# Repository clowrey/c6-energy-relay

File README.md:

# C6 Energy Relay

A Wi-Fi energy meter with two relays, for Home Assistant through ESPHome. It measures the line
voltage and two CT-clamp currents, reports power and energy for each, and switches two loads (or two
contactor coils). It is designed for JLCPCB to build fully assembled. It sits on a DIN rail in a
3D-printed case, inside a plastic junction box.

> **Status:** the design is finished and checked by its own tests (KiCad ERC and DRC with creepage
> rules, schematic parity, JLC files, case fit, ESPHome config). No boards have been made or tested
> yet. Treat it as an untested design: check it yourself before you build one and connect it to
> mains.

| | |
|---|---|
| MCU | ESP32-C5 (DOIT ESPC5-32-H4, 4 MB flash): dual-band 2.4 + 5 GHz Wi-Fi 6, BLE, 802.15.4 (Thread/Zigbee capable), PCB antenna |
| Metering | BL0939 on UART: voltage, 2 × current, 2 × active power, 2 × energy |
| Voltage sense | ZMPT107-1 current-type transformer, fed through 4 × 100 kΩ from the line |
| Current sense | 2 CT clamps with bare leads (100 A : 50 mA type, e.g. SCT-013-000), 0.6 Ω burden each |
| Relays | 2 × Hongfa HF32FV-16 (16 A SPST-NO), dry contacts, for loads up to 10 A |
| Supply | 100–240 V AC: 120 V line–neutral or 240 V leg–leg, chosen at install. HLK-PM01 isolated 5 V, or USB-C on the bench |
| Terminals | all pluggable: 3 × 5.08 mm 15 A (mains in, relay 1, relay 2), 1 × 3.81 mm 4-pole (CTs) |
| GPIO | every unused GPIO on a 2 × 8 header footprint (holes only, nothing fitted) |
| Qwiic | one Qwiic / STEMMA QT port (JST SH, 3.3 V I2C on GPIO2 / GPIO3, 4.7 kΩ pull-ups) |
| Board | 76.4 × 80 mm, 2 layers, every part on the top side, cut away under the antenna |
| Cost | about $14.70 a board for 30, $11.90 for 100, assembled with plugs (estimate, see [below](#ordering-at-jlcpcb)) |

**Contents:** [How it works](#how-it-works) · [Schematic](#schematic) · [Circuit board](#circuit-board) ·
[Case](#case) · [Safety](#safety) · [Wiring](#wiring) · [Firmware](#firmware) ·
[Ordering](#ordering-at-jlcpcb) · [Building from source](#building-it-from-source) · [Licence](#licence)

## How it works

Everything that touches mains is on the left, and everything you can touch (USB-C, the CT terminal,
the GPIO header) is on the right. Three parts bridge the two sides, and each is rated for it: the
HLK-PM01 power module, the ZMPT107-1 voltage transformer and the relays (coil to contact). On the
board the two sides are kept 6.5 mm apart.

- **Power:** the mains input goes through a 1 A slow SMD fuse in **each** line, so a 240 V leg–leg install
  is fused on both legs. The fuses are Hongda 40T ceramic types rated to break 1000 A at 250 V AC (the
  varistor can fail as a short across the line); Littelfuse's 443 fits the same pads but breaks only
  50 A. No copper runs under them. A 10D561K varistor (MOV) clamps surges after the fuses. The potted
  HLK-PM01 makes an isolated 5 V, 600 mA, with a 220 µF solid polymer capacitor on it. On the bench, USB-C powers the board through an SS14 diode
  instead. An AMS1117-3.3 LDO (a JLC Basic part) makes 3.3 V for the ESP32 and the BL0939. Its dropout
  is 1.1 V at 800 mA, and from USB the diode leaves about 4.5 V, so it still regulates through the
  module's 5 GHz transmit peaks (about 400 mA), with little to spare. Its tab sits on a 3.3 V copper area
  that spreads its heat.
- **Voltage:** four 100 kΩ 1206 resistors in series feed about 0.6 mA at 240 V (0.3 mA at 120 V) from the line into
  the ZMPT107-1, a 2 mA : 2 mA current transformer. Its secondary drives a 51 Ω load, and the BL0939 reads
  that voltage on VP (31 mV at 240 V, 34 mV at 264 V). At 120 V the signal is half the 240 V one;
  calibration covers both. The four resistors turn 0.14 W into heat at 240 V (0.04 W at 120 V).
- **Current:** each CT clamp (50 mA at 100 A) works into a 0.6 Ω burden (two 0.3 Ω 1 % resistors,
  centre to ground) right at the terminal, then ferrite beads and a 1 kΩ / 47 nF filter into the
  BL0939. The beads carry only the BL0939's input current, so a failed bead can't open the CT.
- **Metering:** the BL0939 measures continuously and sends readings over a UART (GPIO1 TX, GPIO0 RX, 4800 baud)
  to the ESP32-C5, which runs ESPHome and reports to Home Assistant.
- **Relays:** each relay coil runs from 5 V through an MMBT3904 transistor (470 Ω base resistor,
  about 5 mA, so it saturates fully at the coil's 80–93 mA; 10 kΩ pull-down so it stays off while
  the ESP32 boots) with a 1N4148W flyback diode. GPIO6 and
  GPIO12 drive them. The firmware gives a coil full voltage for 0.3 s, then holds it with PWM at 60 %
  (the relay's datasheet allows a hold at half the rated voltage), so a held coil makes about a third of
  the heat: roughly 0.15 W instead of 0.4 W. The contacts are dry: COM and NO go to their own terminal and switch whatever
  you wire through them.
- **USB-C** goes straight to the ESP32-C5's native USB (GPIO13/14, through 22 Ω series resistors; there is no ESD protection chip),
  for flashing and logs without a USB-serial chip or buttons.

## Schematic

The full schematic is in [`hw/out/schematic.pdf`](hw/out/schematic.pdf) (KiCad 10:
[`hw/c6-energy-relay.kicad_sch`](hw/c6-energy-relay.kicad_sch)). It is generated from
[`hw/design.py`](hw/design.py), one functional block per section, and every pin connects by a net
label.

<details>
<summary><b>Each section, larger</b></summary>

**Mains input, fuses, MOV and the isolated 5 V supply**

**Voltage sense:** the divider into the ZMPT107-1, and its 51 Ω load

**BL0939 metering and the CT inputs**

**5 V and 3.3 V**

**USB-C** (native USB, series resistors, the SS14 power diode)

**ESP32-C5 module, EN and BOOT buttons, status LED, the Qwiic port and the GPIO header**

**Relays and their drivers**

</details>

## Circuit board

76.4 × 80 mm, 2 layers, 1.6 mm, every part on the top side. All the terminals are on the bottom edge,
from left to right: the CTs, the mains input, relay 1 and relay 2. That keeps every wire in one place,
and the low-voltage CT terminal at the far end from the relay contacts. USB-C and the Qwiic port are on
the top edge.
The plug headers stick out 3 mm past the bottom edge, flush with the outside of the case wall, and USB-C
1.25 mm past the top edge, so plugs go in easily with the case on.

The layout is three bands. Along the top: the Qwiic port, USB-C (2.5 mm apart, so both plugs fit side by
side), the LDO and the ESP32-C5 module in the top-right corner. The board is cut away under the module's
antenna (a 26.5 × 6.3 mm notch in the corner), and the copper keep-out around it reaches 3.8 mm past the
module's left side, so there is no board, copper or ground under or beside the antenna. The relays and the
power module are as far from it as the board allows. In the middle: the BL0939 and its input filters in
the left column, the HLK-PM01 beside them, and the GPIO header under the module with the EN and BOOT
buttons and the status LED next to it. Along the bottom: the CT terminal and burdens, the ZMPT107-1, the
fuses with the voltage divider between them, the varistor, and the two relays over their terminals. Every
part has its reference next to it, and the buttons, the LED and every connector pin are named on the
silkscreen.

Small parts keep at least 0.3 mm between their courtyards (the IPC-7351 outline, which already adds
0.25 mm around each part), so there is at least 0.8 mm between any two parts' bodies and pads:
more than JLC's 0.3 mm assembly minimum, with room for a soldering iron.

| Top | Bottom |
|---|---|
|  |  |

| From the front left | Terminals along the bottom edge |
|---|---|
|  |  |

**Mains spacing.** The mains parts are in the bottom half, from the input up to the HLK-PM01 (the
unpoured area on the bottom view), and the low-voltage parts around them. The rules are checked by KiCad's DRC, including its
creepage check, on every build:

| Between | Clearance and creepage |
|---|---|
| any mains net and low voltage (ground, 5 V, 3.3 V, signals) | 6.5 mm |
| L and N/L2, the input and each relay, relay 1 and relay 2 | 4 mm |
| a relay's COM and NO (the open contact sees line voltage) | 4 mm creepage, 3 mm clearance |
| L and N/L2 inside the 5.08 mm terminal and the HLK-PM01's pins | 2 mm (the parts' own pitch); a 1 mm slot between the terminal pins lengthens the surface path |
| the voltage divider's nodes, to each other and to L or N/L2 | 1.5 mm clearance (two resistors apart they see about 120 V) |

The relay contacts carry up to 10 A on 5 mm wide copper areas on both layers, with the solder mask
opened so they can be tinned thicker. The case screws pass through the four mounting holes and can be
touched from the back of the case, so every hole keeps 6.5 mm from mains copper, the same as the
low-voltage side.

**Layers.** The board is routed by hand, with no sharp bend anywhere. The tracks are listed in
[`hw/routes.py`](hw/routes.py) as waypoints, and every straight run is at 0°, 45° or 90°:
[`hw/route.py`](hw/route.py) splits any other leg into a straight run and a 45° run, cuts every right-angle
corner into two 45° bends, and rounds each bend with a small arc (0.5 mm radius for signals, 1.5 × the width
for power and mains). Where tracks run together they cross open board on long 45° runs side by side: the GPIOs
leave the module's pins at 45° and fan down to the header in two 45° bundles, the UART pair runs 45° from the
bus down to the BL0939, and the bus cuts its corners long at 45°. Lanes in a bundle keep their spacing through
every bend. Corners where another branch joins stay
sharp, so the joint stays connected. Signal tracks are 0.2 mm, and ground is poured on both layers and
stitched with vias. The LDO's tab (its 3.3 V output, and how it sheds heat) sits on a solid 3.3 V copper
area of about 46 mm².

| All copper and top silkscreen | Top copper | Bottom copper |
|---|---|---|
|  |  |  |

| Top silkscreen | Top solder mask (openings) |
|---|---|
|  |  |

The GPIO header (J6) carries 3V3, 5V, GND and GPIO 4, 7, 8, 9, 10, 11, 15, 23, 24, 25, 26 and 27. Power
comes first, then ground, then the GPIOs in the order they leave the module (one row reads 3V3, GND, 7, 9,
27, 23, 11, 26; the other 5V, GND, 8, 10, 4, 15, 24, 25), so a sensor's supply, ground and signal wires sit
side by side. GPIO27 has a 10 kΩ pull-up (R19): the ESP32-C5 needs it high at reset for USB flashing.
The Qwiic port (J7, at the left end of the top edge) is a 4-pin JST SH socket for 3.3 V I2C sensors and
displays: pin 1 GND, 2 3V3, 3 SDA (GPIO2), 4 SCL (GPIO3), with 4.7 kΩ pull-ups to 3V3. GPIO2 and GPIO3 are
strapping pins (MTMS and MTDI), but the pull-ups hold them high at reset, which is what they need there.
The silkscreen marks the strapping pins on the header (7, 25, 26, 27) with `*`: keep them free of pull-downs at reset. The top side names each plug: the CT pins
behind their terminal, `RELAY 1` / `RELAY 2` beside theirs with `COM` and `NO` each over its own contact's copper, `MAINS`, `USB` and `QWIIC`. The Qwiic pins are named in pin order below the socket (`SCL SDA 3V3 GND`)
and again on the bottom side, in the order you see them from there.
The bottom side names every terminal pin.

## Case

Three printed parts, built in build123d from the board's own dimensions ([`case/case.py`](case/case.py)):

- **Cover:** the front shell, with a pillar at each of the board's four mounting holes. The plugs
  stick out through openings in the bottom wall, USB-C and the Qwiic port through the top; the wall is solid below the
  board, so nothing slips in under it to the mains solder joints. There are vents in the top wall
  beside the USB-C and in the right wall above the relays (none beside mains parts). The front face is closed; a short tube carries the status LED's light
  to a 0.6 mm thin window. The front face names every opening and its pins (MAINS L N, RELAY 1 and 2
  COM NO, CT1 and CT2 + −, USB, QWIIC), cut 0.4 mm deep. The Qwiic opening is 13 × 8 mm: the small plug ends
  inside the wall, so the opening leaves 3 mm each side to grip it, and it is too low for a finger.
- **Base:** the sealed back plate. Its only openings are the four screw holes, so nothing pushed in
  from the back (a screwdriver, the metal DIN rail) can reach the mains parts behind the board. A
  standoff rises from it to each mounting hole, and a rim locates it inside the cover's walls. A
  0.4 mm deep pocket in its back gives the clip's moving parts room to slide.
- **DIN clip:** screwed under the base, it clips the case onto a TS35 rail.
  - **Hook (top):** 65 mm long, with a 3.5 mm thick wall and a 2.2 mm thick lip that reaches 2 mm
    over the rail's flange. Five ribs behind the wall stop it bending back off the rail.
  - **Latch (bottom):** a 20 mm wide block with the same wall and lip. It rides on four 1.2 mm spring
    beams cut into the clip plate, which bend in the plate's own plane, so the block slides down
    2.4 mm to clear the flange while the beams stay under half of PETG's yield strain. The beams are
    anchored clear of the screw at the left (it sits in their band), so the latch is a little right
    of centre. The
    lip's underside is a 45° ramp: rock the case onto the rail and it snaps on. Two straps printed
    over the pull tab's channel stop the latch twisting away from the case.
  - **To take it off the rail,** pull the tab at the clip's bottom edge down: put a screwdriver in
    its slot and lever.

**Four screws hold everything:** M3 × 16 countersunk, from the back through the clip, the base, its
standoff and the board, self-tapping into 2.8 mm pilot holes in the cover's pillars (no inserts). The
board is clamped between the standoffs and the pillars, and the heads sit flush in the clip. To
assemble, lay the cover face down, drop the board in (components down) onto the pillars, put the
base and then the clip on, and fit the four screws. Nothing inside the walls stands between the
board and the open back, and a test checks that.

| Exploded | Board in the cover, from the back |
|---|---|
|  |  |

| On a DIN rail, from the back | The DIN clip: ribbed hook (top), latch on its spring beams and pull tab (bottom) |
|---|---|
|  |  |

Print in PETG (the latch has to flex): 0.2 mm layers, 3 walls. Print the cover on its front face and
the base on its back face (standoffs up), both without supports. Print the clip on its flat face (hook
and latch up), so the spring beams bend along the layers, with supports under the hook's and latch's
2 mm lips only: not under the two straps over the pull tab, which bridge. STEP files and print-oriented STL files are in
[`case/out`](case/out).

## Safety

**This board connects to mains voltage.** Build, wire and install it only if you are competent to do
mains work, and power it only inside its case, inside a closed plastic enclosure.

- The HLK-PM01, the ZMPT107-1 and the relays are the isolation barrier. Everywhere else, mains is
  kept 6.5 mm from the low-voltage side.
- USB-C, the CT terminal and the GPIO header are on the isolated side. Even so, **don't connect USB
  to a board that is wired to mains**: flash it on the bench first, then update it over Wi-Fi.
- There is no protective earth. The board and case are for a plastic enclosure only.
- The relays are rated 16 A. Keep loads at or below 10 A, and use an external contactor above that.
- No metal near the board: the warning on the bottom silkscreen says so too.

## Wiring

All the terminals unplug: wire each plug first, then plug it in. Looking at the component side, left
to right:

| Terminal | Pins | Use |
|---|---|---|
| J4 (3.81 mm) | CT1+, CT1−, CT2+, CT2− | the two CT clamps (low voltage) |
| J1 (5.08 mm) | L, N/L2 | supply and voltage reference |
| J2 (5.08 mm) | COM, NO | relay 1, dry contact |
| J3 (5.08 mm) | COM, NO | relay 2, dry contact |

- **120 V line–neutral:** line to `L`, neutral to `N/L2`.
- **240 V leg–leg (US split phase):** L1 to `L`, L2 to `N/L2`. Both inputs are fused, so either
  way works. The voltage reading is then the leg–leg voltage.
- **Relays:** dry contacts, so they switch whatever you wire through them, for example `L` → COM and
  NO → load. A contactor coil is wired the same way.
- **CTs:** clamp each CT around one conductor. If a channel reads negative power, turn the clamp
  around or swap its two wires.

## Firmware

[`firmware/c6-energy-relay.yaml`](firmware/c6-energy-relay.yaml) is a starter ESPHome config. It has:

- the BL0939 sensors: voltage, current, power and energy;
- `Relay 1` and `Relay 2` switches, always off after a reboot or power cut, with the coil hold above
  (`coil_hold: "100%"` turns it off);
- the status LED;
- an I2C bus on the Qwiic port (GPIO2 / GPIO3), which scans for devices at boot; add your sensor to it;
- the BOOT button, which toggles relay 1. It's on the board, inside the closed case, so it's for the
  bench.

Add a `secrets.yaml` with `wifi_ssid`, `wifi_password`, `api_key`, `ota_password` and
`ap_password`. Flash it over USB-C (native USB, no buttons needed), then update over Wi-Fi from then
on. Logs go to the USB port, which leaves the ESP32's UART to the BL0939.

| GPIO | Use | GPIO | Use |
|---|---|---|---|
| 1 | UART TX to BL0939 RX | 6 | relay 1 |
| 0 | UART RX from BL0939 TX | 12 | relay 2 |
| 13 / 14 | USB D− / D+ | 5 | status LED |
| 28 | BOOT button (strapping) | 27 | 10 kΩ pull-up (strapping, on the header) |
| 2 / 3 | Qwiic SDA / SCL (strapping, held high by the pull-ups) | | |

**Calibration:** with a known resistive load and a meter, set each `*_cal` substitution to
(its starting value × meter reading ÷ reported value). The energy sensors use the power factors.
The starting values convert ESPHome's BL0939 scaling (a 1 mΩ shunt and a 0.51 kΩ / 1.95 MΩ divider) to
this board: current × 3.33 (CTs give 0.3 mV/A), voltage × 2.05 (0.1275 mV/V) and power × 6.84.

## Ordering at JLCPCB

The order files are in [`hw/out/jlc`](hw/out/jlc):

1. **PCB:** upload `gerbers.zip`: 2 layers, 1.6 mm, 1 oz, HASL (with lead or lead-free), any colour. JLC's
   default finish is now OSP, which rules out Economic PCBA.
2. **Assembly:** choose **Economic PCBA**, top side, and upload `bom.csv` and `cpl.csv`. The ESP32-C5
   module has castellated edge pads, so it needs no X-ray inspection; JLC hand-solders the through-hole
   parts.
3. **Check the placement preview before paying.** Every part should sit on its footprint and point
   the right way. Pay most attention to:
   - the ESP32-C5 module (its antenna end at the top board edge) and USB-C;
   - the Qwiic socket (J7): its opening must face the top board edge;
   - the BL0939;
   - the LDO (U3): its wide tab is pin 2, on the 3.3 V copper area;
   - the diodes and transistors, and the polymer capacitor (C14): its + side faces the HLK-PM01;
   - both buttons. A button turned 90° holds EN or BOOT low.

   All 33 parts were checked this way in JLC's preview on 2026-11-24, against the pad positions in the
   board file. The board has been laid out again since (same parts and footprints), and JLC changes its
   part drawings now and then, so look again before paying.
4. **Plugs:** add the loose plugs from `plugs.csv` to the same order as parts: 3 × DB2EK-5.08-2P and
   1 × WJ15EDGK-3.81-4P per board.

Cost estimate from [`cost.md`](hw/out/jlc/cost.md). Part prices are live JLC prices from 2026-11-24;
the fees, PCB and shipping figures are estimates, so check the real quote.

| Boards | Total | Per board |
|---|---|---|
| 10 | $200 | $20.04 |
| 20 | $332 | $16.62 |
| 30 | $441 | $14.70 |
| 50 | $657 | $13.14 |
| 100 | $1191 | $11.91 |

JLC's own quote on 2026-11-23 for 10 boards with this module (Economic PCBA, top side) was **$163.49**
before shipping, duties and the loose plugs: $5.00 for the boards and $158.49 for assembly, of which
$108.19 is parts, $27.81 Extended-part fees and $9.79 setup and stencil. That quote still had the
earlier LDO, an Extended part; the AMS1117 is a Basic part. With Standard PCBA, 30 boards with the
earlier ESP32-C6-MINI-1 came to $469.65, including a $24.90 X-ray inspection for that module's
hidden pads.

The most expensive parts per board, at 30 boards:

| Part | Cost per board |
|---|---|
| ESPC5-32-H4 (ESP32-C5) | $2.80 |
| HLK-PM01 | $2.17 |
| two relays | $1.88 |
| BL0939 | $0.68 |
| ZMPT107-1 | $0.41 |

The estimate counts $3 per order for each of the 13 Extended parts. The passives are JLC Basic parts
wherever one fits (the 100 kΩ divider, the 51 Ω load, the 47 nF filter capacitors, the 10 µF capacitors);
the 0.3 Ω burdens and the 220 µF polymer capacitor have no Basic equivalent.

## Building it from source

Everything is generated by scripts; edit the scripts, not the KiCad files. `KPY` is KiCad 10's own
Python (`"C:\Program Files\KiCad\10.0\bin\python.exe"` on Windows); the other steps use a normal
Python 3.11+ with `pip install -r requirements-dev.txt` (build123d, pytest) plus PyMuPDF, Pillow and
VTK for the images.

| Step | Command |
|---|---|
| symbols, footprints, 3D bodies | `KPY hw/gen_lib.py`, then `python -m hw.gen_3d` |
| schematic and project | `python -m hw.gen_sch` |
| board: placement, rules, zones, silkscreen | `KPY hw/gen_pcb.py` |
| tracks and zone fill | `KPY hw/route.py` |
| board STEP | `kicad-cli pcb export step --drill-origin --subst-models -o hw/out/board.step hw/c6-energy-relay.kicad_pcb` |
| schematic PDF | `kicad-cli sch export pdf -o hw/out/schematic.pdf hw/c6-energy-relay.kicad_sch` |
| JLC files and cost sheet | `KPY hw/export_jlc.py` |
| case | `python case/case.py` |
| README images | `python docs/make_images.py` and `python docs/block_diagram.py` |
| tests | `python -m pytest` |

The tests run:

- KiCad's ERC, and its DRC with the creepage rules and schematic parity;
- the antenna keep-out and the mounting-hole spacing;
- a silkscreen check;
- the JLC files against the board;
- live JLC stock for 30 boards;
- the case fit: the board's path in, board, plugs, screws, openings, the sealed back, flat
  printing and the DIN clip (including the latch's travel and spring strain);
- the ESP32 pins in the firmware against the design;
- ESPHome validating the config, through `esphome` on the PATH, `$ESPHOME_CMD` or `esphome-wsl`
  inside WSL.

The circuit lives in [`hw/design.py`](hw/design.py) and the parts, with their LCSC numbers, in
[`hw/parts.py`](hw/parts.py). The schematic, board, BOM and firmware pin check all read from those
two files.

| Folder | Contents |
|---|---|
| `hw/` | the generators, KiCad project, local symbol and footprint library (`lib/`) |
| `hw/out/` | schematic PDF, board STEP, JLC files |
| `case/` | the case script and its STEP/STL output |
| `firmware/` | ESPHome config |
| `docs/` | the scripts that make the README images, and the images |
| `tests/` | pytest checks for all of the above |

## Licence

- **Hardware** (the circuit board and the case: everything in `hw/` and `case/`, including the scripts
  that generate them, and the images): [CERN-OHL-P-2.0](LICENSES/CERN-OHL-P-2.0.txt), the permissive
  CERN Open Hardware Licence.
- **Software** (the ESPHome config, the tests and the image scripts): [MIT](LICENSES/MIT.txt).

See [`LICENSE`](LICENSE). Both come with no warranty. This board connects to mains, so building,
installing and using it is at your own risk.

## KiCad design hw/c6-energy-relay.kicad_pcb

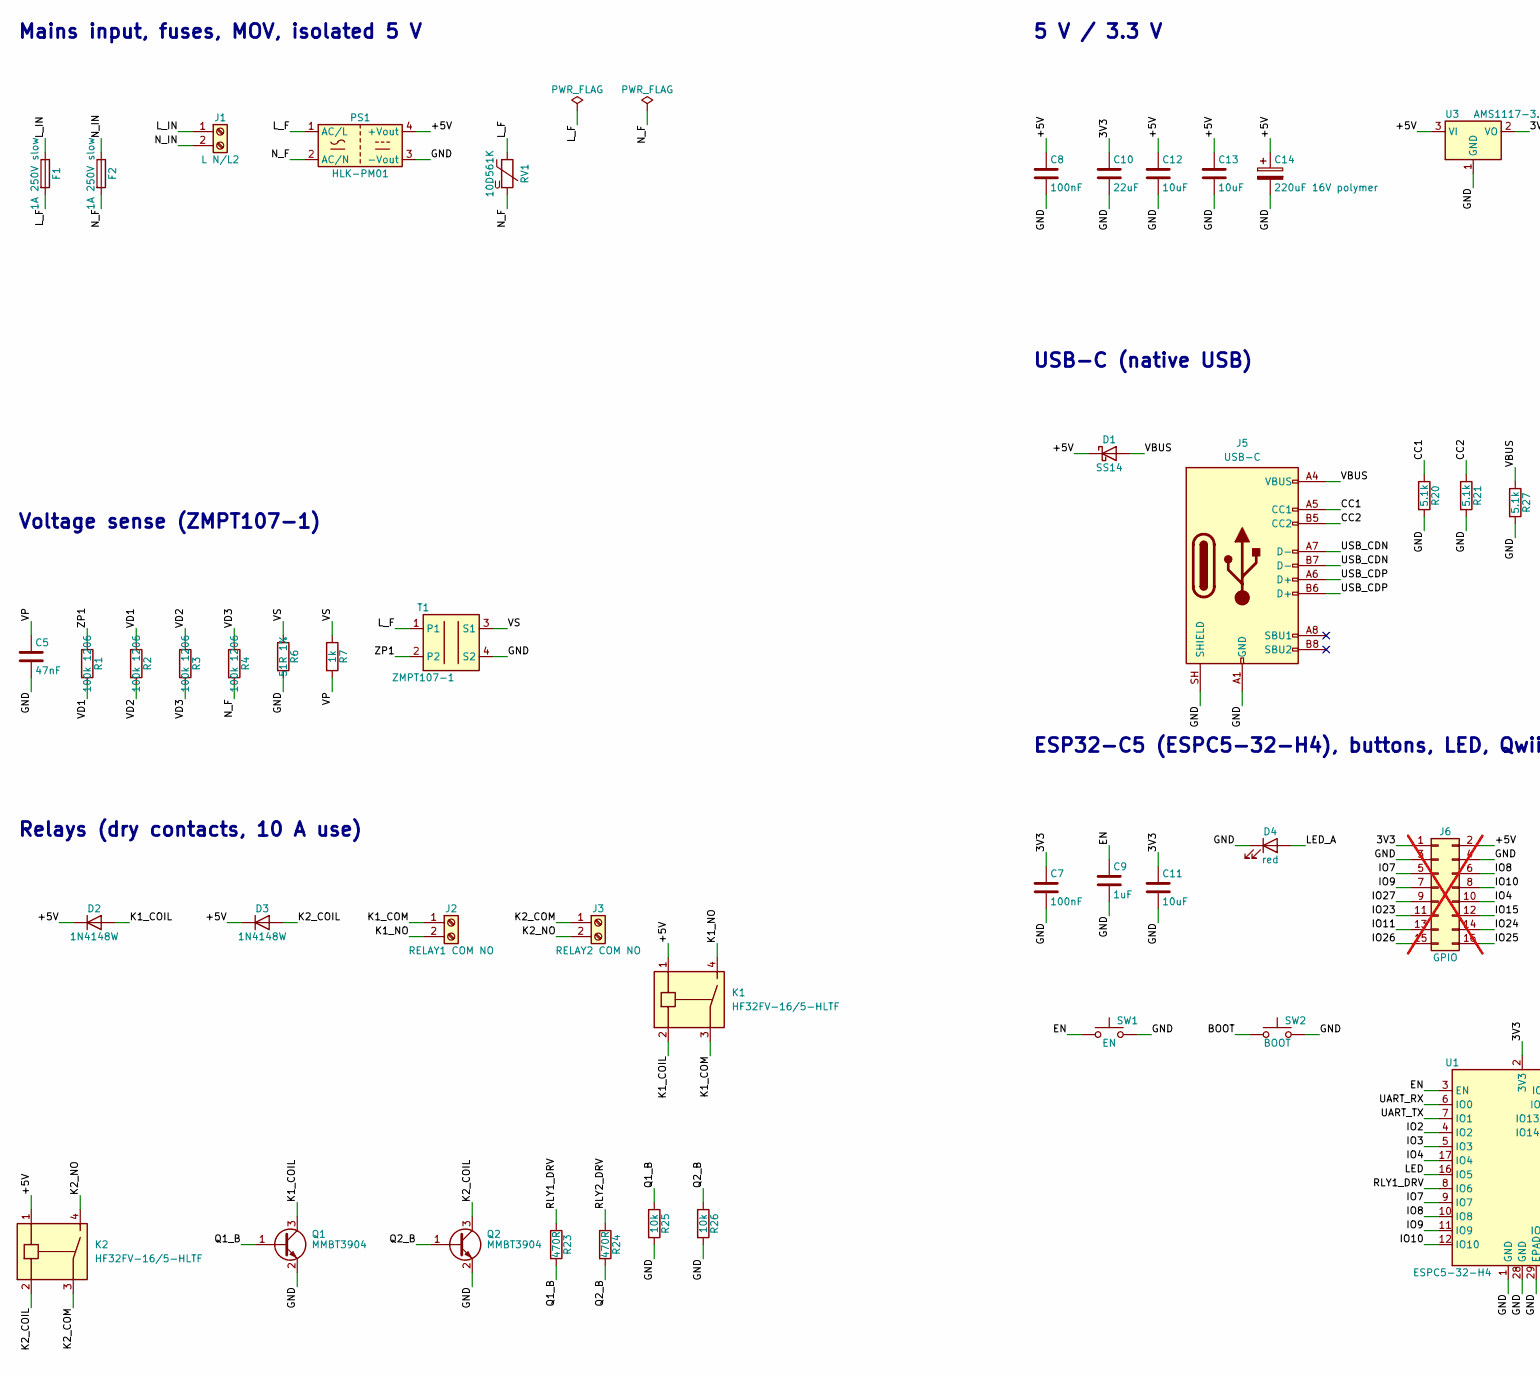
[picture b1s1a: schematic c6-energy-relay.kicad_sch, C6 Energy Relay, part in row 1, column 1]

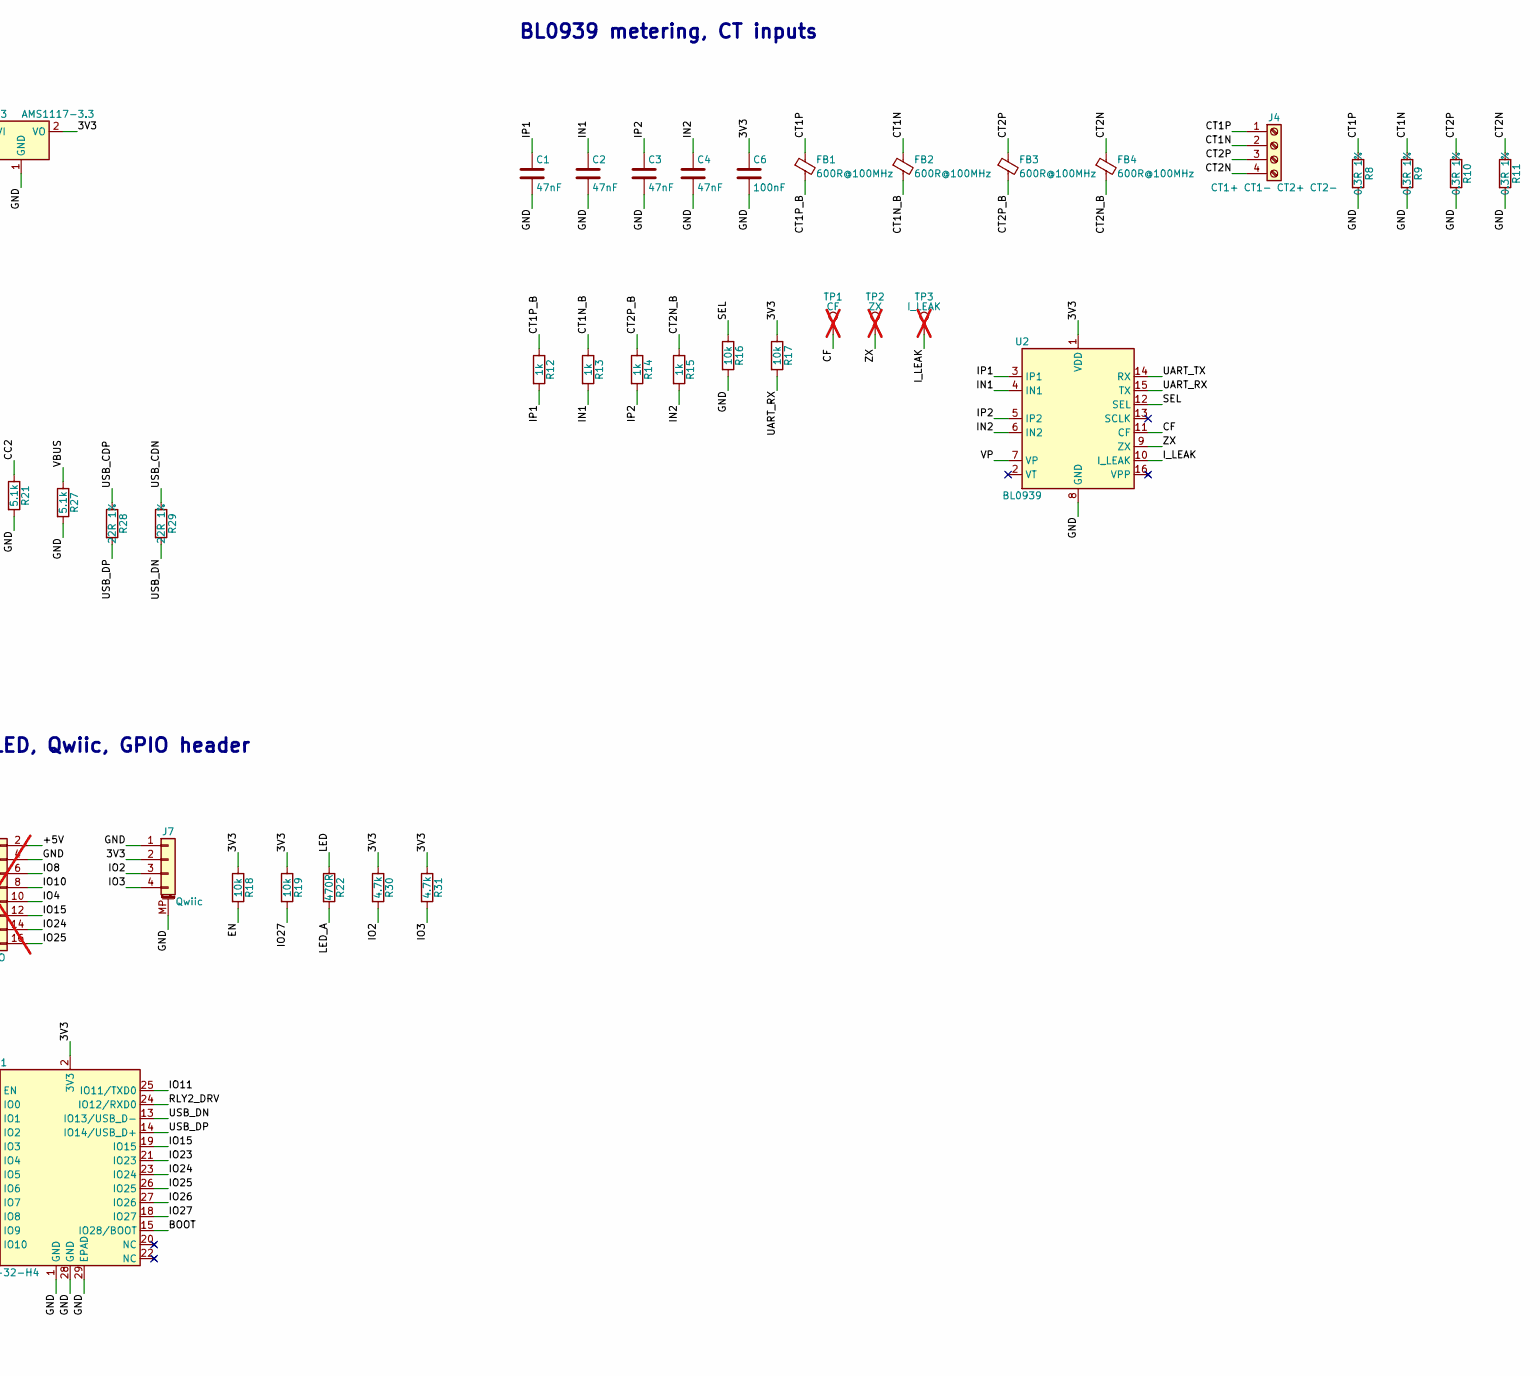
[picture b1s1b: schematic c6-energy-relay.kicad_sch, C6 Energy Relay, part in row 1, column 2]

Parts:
C1, C2, C3, C4, C5: 47nF; C_0603_1608Metric; MPN CL10B473KB8NNNC; LCSC C1622
C6, C7, C8: 100nF; C_0603_1608Metric; LCSC C14663
C9: 1uF; C_0603_1608Metric; LCSC C15849
C10: 22uF; C_0805_2012Metric; LCSC C45783
C11, C12, C13: 10uF; C_0805_2012Metric; LCSC C15850
C14: 220uF 16V polymer; CP_Elec_6.3x7.7; MPN MA16V220M6X8; LCSC C46550461
D1: SS14; D_SMA; MPN SS14; LCSC C2480
D2, D3: 1N4148W; D_SOD-123; MPN 1N4148W; LCSC C81598
D4: red; LED_0603_1608Metric; MPN KT-0603R; LCSC C2286
F1, F2: 1A 250V slow; Fuse_SMD_10.1x3.1; MPN 40T 1A250V; LCSC C48392807
FB1, FB2, FB3, FB4: 600R@100MHz; L_0603_1608Metric; MPN GZ1608D601TF; LCSC C1002
J1: L N/L2; DB2ER-5.08-02P; MPN DB2ER-5.08-2P-GN; LCSC C395730
J2: RELAY1 COM NO; DB2ER-5.08-02P; MPN DB2ER-5.08-2P-GN; LCSC C395730
J3: RELAY2 COM NO; DB2ER-5.08-02P; MPN DB2ER-5.08-2P-GN; LCSC C395730
J4: CT1+ CT1- CT2+ CT2-; WJ15EDGRC-3.81-04P; MPN WJ15EDGRC-3.81-04P; LCSC C7245
J5: USB-C; USB_C_Receptacle_HRO_TYPE-C-31-M-12; MPN TYPE-C-31-M-12; LCSC C165948
J6: GPIO; PinHeader_2x08_P2.54mm_Vertical; not fitted
J7: Qwiic; JST_SH_SM04B-SRSS-TB_1x04-1MP_P1.00mm_Horizontal; MPN SM04B-SRSS-TB(LF)(SN); LCSC C160404
K1, K2: HF32FV-16/5-HLTF; HF32FV-16; MPN HF32FV-16/5-HLTF(590); LCSC C2976831
PS1: HLK-PM01; Converter_ACDC_Hi-Link_HLK-PMxx; MPN HLK-PM01; LCSC C209903
Q1, Q2: MMBT3904; SOT-23; MPN MMBT3904; LCSC C20526
R1, R2, R3, R4: 100k 1206; R_1206_3216Metric; MPN 1206W4F1003T5E; LCSC C17900
R6: 51R 1%; R_0603_1608Metric; MPN 0603WAF510JT5E; LCSC C23197
R7, R12, R13, R14, R15: 1k; R_0603_1608Metric; LCSC C21190
R8, R9, R10, R11: 0.3R 1%; R_1206_3216Metric; LCSC C59882
R16, R17, R18, R19, R25, R26: 10k; R_0603_1608Metric; LCSC C25804
R20, R21, R27: 5.1k; R_0603_1608Metric; LCSC C23186
R22, R23, R24: 470R; R_0603_1608Metric; LCSC C23179
R28, R29: 22R 1%; R_0603_1608Metric; LCSC C23345
R30, R31: 4.7k; R_0603_1608Metric; LCSC C23162
RV1: 10D561K; RV_Disc_D12mm_W6.1mm_P7.5mm; MPN 10D561K; LCSC C233178
SW1: EN; SW_Push_1P1T_XKB_TS-1187A; MPN TS-1187A-B-A-B; LCSC C318884
SW2: BOOT; SW_Push_1P1T_XKB_TS-1187A; MPN TS-1187A-B-A-B; LCSC C318884
T1: ZMPT107-1; MPN ZMPT107-1; LCSC C125191
TP1: CF; TestPoint_Pad_D1.0mm; not fitted
TP2: ZX; TestPoint_Pad_D1.0mm; not fitted
TP3: I_LEAK; TestPoint_Pad_D1.0mm; not fitted
U1: ESPC5-32-H4; ESPC5-32; MPN ESPC5-32-H4; LCSC C52139914
U2: BL0939; SOIC-16_3.9x9.9mm_P1.27mm; MPN BL0939; LCSC C2836697
U3: AMS1117-3.3; SOT-223-3_TabPin2; MPN AMS1117-3.3; LCSC C6186

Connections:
/3V3: C6.1, C7.1, C10.1, C11.1, J6.1, J7.2, R17.1, R18.1, R19.1, R30.1, R31.1, U1.2 (3V3), U2.1 (VDD), U3.2 (VO)
/+5V: C8.1, C12.1, C13.1, C14.1, D1.1 (K), D2.1 (K), D3.1 (K), J6.2, K1.1 (A1), K2.1 (A1), PS1.4 (+Vout), U3.3 (VI)
/BOOT: SW2.1, U1.15 (IO28/BOOT)
/CC1: J5.A5 (CC1), R20.1
/CC2: J5.B5 (CC2), R21.1
/CF: TP1.1, U2.11 (CF)
/CT1N: FB2.1, J4.2, R9.1
/CT1N_B: FB2.2, R13.1
/CT1P: FB1.1, J4.1, R8.1
/CT1P_B: FB1.2, R12.1
/CT2N: FB4.1, J4.4, R11.1
/CT2N_B: FB4.2, R15.1
/CT2P: FB3.1, J4.3, R10.1
/CT2P_B: FB3.2, R14.1
/EN: C9.1, R18.2, SW1.1, U1.3 (EN)
/GND: C1.2, C2.2, C3.2, C4.2, C5.2, C6.2, C7.2, C8.2, C9.2, C10.2, C11.2, C12.2, C13.2, C14.2, D4.1 (K), J5.A1 (GND), J5.A12 (GND), J5.B1 (GND), J5.B12 (GND), J5.SH (SHIELD), J6.3, J6.4, J7.1, J7.MP (MountPin), PS1.3 (-Vout), Q1.2 (E), Q2.2 (E), R6.2, R8.2, R9.2, R10.2, R11.2, R16.2, R20.2, R21.2, R25.2, R26.2, R27.2, SW1.2, SW2.2, T1.4 (S2), U1.1 (GND), U1.28 (GND), U1.29 (EPAD), U2.8 (GND), U3.1 (GND)
/IN1: C2.1, R13.2, U2.4 (IN1)
/IN2: C4.1, R15.2, U2.6 (IN2)
/IO2: J7.3, R30.2, U1.4 (IO2)
/IO3: J7.4, R31.2, U1.5 (IO3)
/IO4: J6.10, U1.17 (IO4)
/IO7: J6.5, U1.9 (IO7)
/IO8: J6.6, U1.10 (IO8)
/IO9: J6.7, U1.11 (IO9)
/IO10: J6.8, U1.12 (IO10)
/IO11: J6.13, U1.25 (IO11/TXD0)
/IO15: J6.12, U1.19 (IO15)
/IO23: J6.11, U1.21 (IO23)
/IO24: J6.14, U1.23 (IO24)
/IO25: J6.16, U1.26 (IO25)
/IO26: J6.15, U1.27 (IO26)
/IO27: J6.9, R19.2, U1.18 (IO27)
/IP1: C1.1, R12.2, U2.3 (IP1)
/IP2: C3.1, R14.2, U2.5 (IP2)
/I_LEAK: TP3.1, U2.10 (I_LEAK)
/K1_COIL: D2.2 (A), K1.2 (A2), Q1.3 (C)
/K1_COM: J2.1, K1.3 (COM)
/K1_NO: J2.2, K1.4 (NO)
/K2_COIL: D3.2 (A), K2.2 (A2), Q2.3 (C)
/K2_COM: J3.1, K2.3 (COM)
/K2_NO: J3.2, K2.4 (NO)
/LED: R22.1, U1.16 (IO5)
/LED_A: D4.2 (A), R22.2
/L_F: F1.2, PS1.1 (AC/L), RV1.1, T1.1
/L_IN: F1.1, J1.1
/N_F: F2.2, PS1.2 (AC/N), R4.2, RV1.2
/N_IN: F2.1, J1.2
/Q1_B: Q1.1 (B), R23.2, R25.1
/Q2_B: Q2.1 (B), R24.2, R26.1
/RLY1_DRV: R23.1, U1.8 (IO6)
/RLY2_DRV: R24.1, U1.24 (IO12/RXD0)
/SEL: R16.1, U2.12 (SEL)
/UART_RX: R17.2, U1.6 (IO0), U2.15 (TX)
/UART_TX: U1.7 (IO1), U2.14 (RX)
/USB_CDN: J5.A7 (D-), J5.B7 (D-), R29.1
/USB_CDP: J5.A6 (D+), J5.B6 (D+), R28.1
/USB_DN: R29.2, U1.13 (IO13/USB_D-)
/USB_DP: R28.2, U1.14 (IO14/USB_D+)
/VBUS: D1.2 (A), J5.A4 (VBUS), J5.A9 (VBUS), J5.B4 (VBUS), J5.B9 (VBUS), R27.1
/VD1: R1.2, R2.1
/VD2: R2.2, R3.1
/VD3: R3.2, R4.1
/VP: C5.1, R7.2, U2.7 (VP)
/VS: R6.1, R7.1, T1.3 (S1)
/ZP1: R1.1, T1.2
/ZX: TP2.1, U2.9 (ZX)

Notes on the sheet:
Mains input, fuses, MOV, isolated 5 V
Voltage sense (ZMPT107-1)
Relays (dry contacts, 10 A use)
5 V / 3.3 V
USB-C (native USB)
ESP32-C5 (ESPC5-32-H4), buttons, LED, Qwiic, GPIO header
BL0939 metering, CT inputs

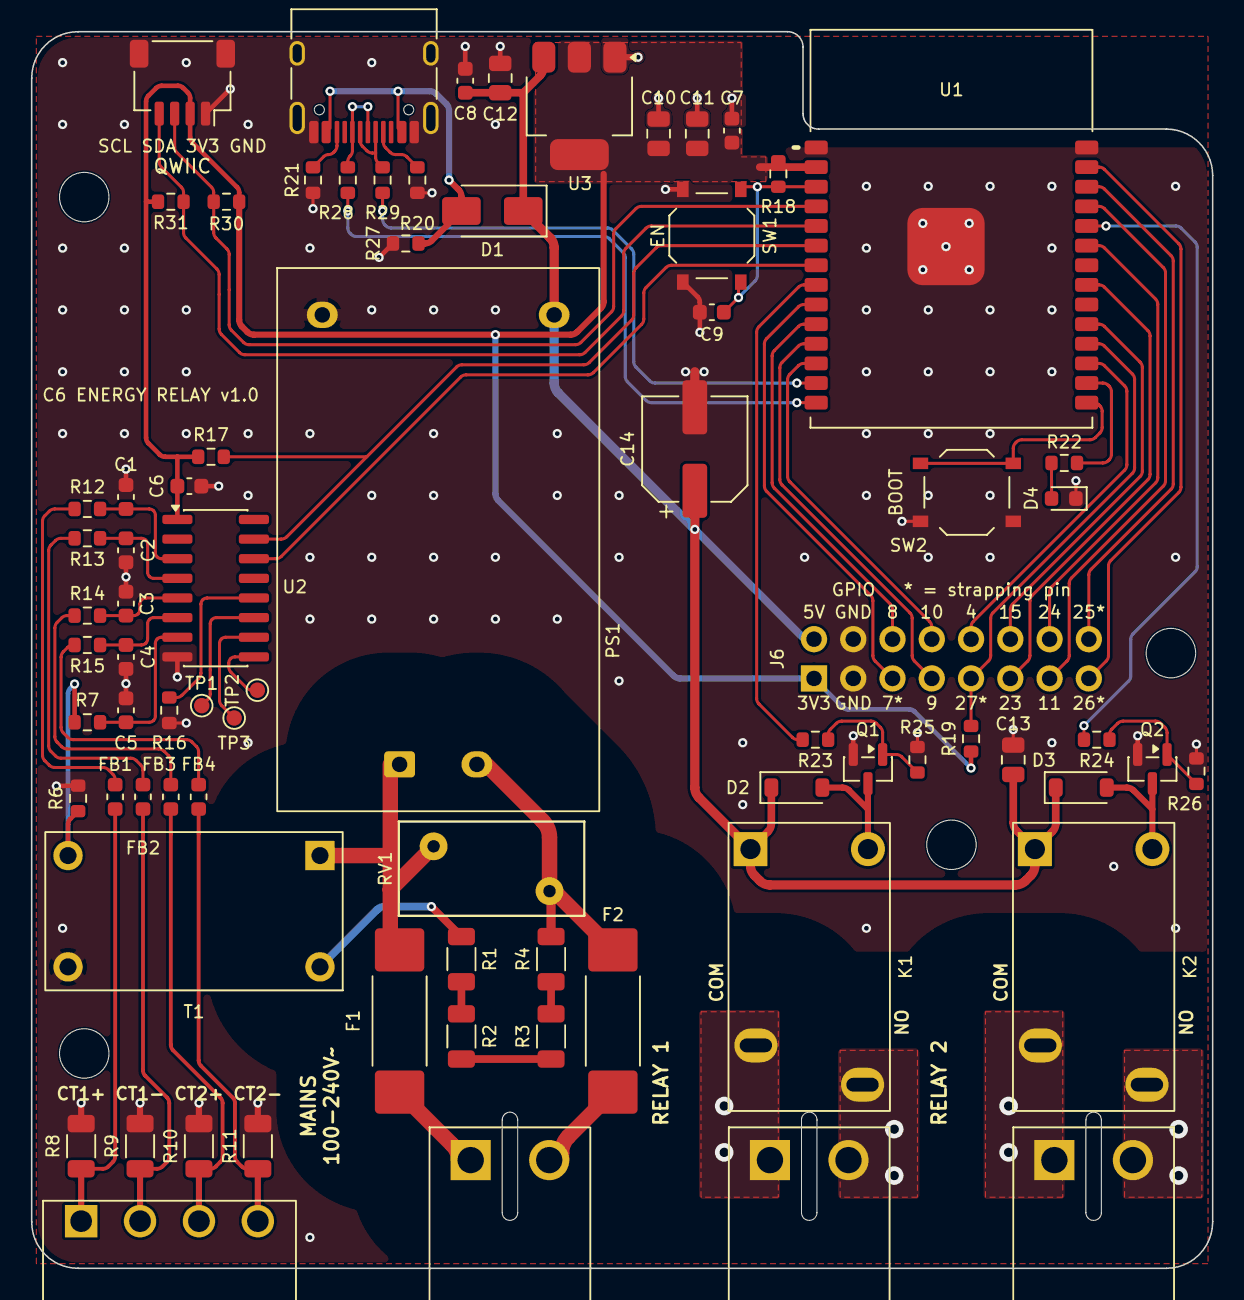
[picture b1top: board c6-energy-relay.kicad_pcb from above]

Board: 2 copper layers, 76.4 x 80.0 mm, 80 parts (0 on the bottom side), 66 nets.

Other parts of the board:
H1, H2, H3, H4: MountingHole_3.2mm_M3

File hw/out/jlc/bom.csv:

Comment,Designator,Footprint,LCSC
CL10B473KB8NNNC,"C1,C2,C3,C4,C5",C_0603_1608Metric,C1622
22uF,C10,C_0805_2012Metric,C45783
10uF,"C11,C12,C13",C_0805_2012Metric,C15850
MA16V220M6X8,C14,CP_Elec_6.3x7.7,C46550461
100nF,"C6,C7,C8",C_0603_1608Metric,C14663
1uF,C9,C_0603_1608Metric,C15849
SS14,D1,D_SMA,C2480
1N4148W,"D2,D3",D_SOD-123,C81598
KT-0603R,D4,LED_0603_1608Metric,C2286
40T 1A250V,"F1,F2",Fuse_SMD_10.1x3.1,C48392807
GZ1608D601TF,"FB1,FB2,FB3,FB4",L_0603_1608Metric,C1002
DB2ER-5.08-2P-GN,"J1,J2,J3",DB2ER-5.08-02P,C395730
WJ15EDGRC-3.81-04P,J4,WJ15EDGRC-3.81-04P,C7245
TYPE-C-31-M-12,J5,USB_C_Receptacle_HRO_TYPE-C-31-M-12,C165948
SM04B-SRSS-TB(LF)(SN),J7,JST_SH_SM04B-SRSS-TB_1x04-1MP_P1.00mm_Horizontal,C160404
HF32FV-16/5-HLTF(590),"K1,K2",HF32FV-16,C2976831
HLK-PM01,PS1,Converter_ACDC_Hi-Link_HLK-PMxx,C209903
MMBT3904,"Q1,Q2",SOT-23,C20526
1206W4F1003T5E,"R1,R2,R3,R4",R_1206_3216Metric,C17900
10k,"R16,R17,R18,R19,R25,R26",R_0603_1608Metric,C25804
5.1k,"R20,R21,R27",R_0603_1608Metric,C23186
470R,"R22,R23,R24",R_0603_1608Metric,C23179
22R 1%,"R28,R29",R_0603_1608Metric,C23345
4.7k,"R30,R31",R_0603_1608Metric,C23162
0603WAF510JT5E,R6,R_0603_1608Metric,C23197
1k,"R7,R12,R13,R14,R15",R_0603_1608Metric,C21190
0.3R 1%,"R8,R9,R10,R11",R_1206_3216Metric,C59882
10D561K,RV1,RV_Disc_D12mm_W6.1mm_P7.5mm,C233178
TS-1187A-B-A-B,"SW1,SW2",SW_Push_1P1T_XKB_TS-1187A,C318884
ZMPT107-1,T1,ZMPT107-1,C125191
ESPC5-32-H4,U1,ESPC5-32,C52139914
BL0939,U2,SOIC-16_3.9x9.9mm_P1.27mm,C2836697
AMS1117-3.3,U3,SOT-223-3_TabPin2,C6186

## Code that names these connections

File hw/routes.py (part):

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J1L, J1N = (at("J1")[0] - 0.8, at("J1")[1]), (at("J1")[0] + 5.08 + 0.8, at("J1")[1])
t("L_IN", J1L, (J1L[0], FPY + (J1L[0] - at("F1")[0])), ("F1", "1"), w=1.0)
t("N_IN", J1N, (J1N[0], FPY + (at("F2")[0] - J1N[0])), ("F2", "1"), w=1.0)
# L_F: one straight run from inside the fuse's pin up into the supply's L pin, on the pins' left side (4 mm from its
# N pin); the MOV and T1's primary branch off it
LX = PX - 0.6
RVL = at("RV1")                     # the MOV's L pin
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t("L_F", (LX, at("F1")[1] - 4.6), LFM, LFT, (LX, at("PS1")[1]), w=1.0)
t("L_F", LFM, ("RV1", "1"), w=1.0)
t("L_F", LFT, ("T1", "1"), w=1.0)
# N_F: 45 degrees from the fuse into the MOV's N pin, then the divider's end below it and the supply's N pin above
RVN = (RVL[0] + 7.5, RVL[1] + 2.9)                        # the MOV's N pin
t("N_F", ("F2", "2"), (at("F2")[0] - (FPY - 9.2 - RVN[1]), RVN[1]), w=1.0)
t("N_F", (at("R4")[0], RVN[1]), ("R4", "2"), w=0.6)
PSN = (at("PS1")[0] + 5.6, at("PS1")[1])   # inside the supply's N pin, on its right side
t("N_F", RVN, (RVN[0], PSN[1] + (RVN[0] - PSN[0])), PSN, w=1.0)
# ZP1 crosses L_F underneath, above the fuse's pin, and comes up 45 degrees to the divider's first resistor
ZPY = at("R1")[1] - 1.46 - 1.94     # R1's ZP1 pin less the via's 45-degree run
ZPV = (at("R1")[0] - 1.94, ZPY)
T1Z = (at("T1")[0] + 8.15, at("T1")[1] + 3.6)            # T1's primary return pin (ZP1)
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# ======================================================================== CT inputs & BL0939 ===
# terminal -> burden; then each line leaves its burden through the gap beside it and runs up under T1's body
# (between its secondary pins and 6.5 mm from its primary) to its bead
for pin, rb, ct in (("1", "R8", "CT1P"), ("2", "R9", "CT1N"), ("3", "R10", "CT2P"), ("4", "R11", "CT2N")):
    t(ct, ("J4", pin), (rb, "1"), w=0.4)
BY = at("R8")[1]                    # burden row
FBY = at("FB1")[1]                  # bead row
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b("VS", ("T1", "3"), VSV, w=0.3, vias=[VSV])
t("VS", VSV, ("R7", "1"), w=0.3)

# BL0939 control pins: out under the chip's body and down to the SEL pull-down and the three test pads
for i, (pin, net, target) in enumerate((("12", "SEL", ("R16", "1")), ("11", "CF", ("TP1", "1")),
                                        ("10", "I_LEAK", ("TP3", "1")), ("9", "ZX", ("TP2", "1")))):
    lx = U2X - 0.95 + 0.6 * i
    px, py = u2pin(pin)
    # SEL goes a little further down first, so its 45-degree run clears pin 8's ground via
    t(net, ("U2", pin), (lx, py), (lx, U2Y + (5.7 if net == "SEL" else 5.3)), target, radii=[None, 0.4],
      end=(-1, 0) if net == "SEL" else None)
R16V = (at("R16")[0] + 1.1, at("R16")[1] + 0.825)
t("GND", ("R16", "2"), R16V, vias=[R16V])
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# the UART pair leaves the run 45 degrees down to the BL0939, side by side, each ending level with its pin; RX's
# pull-up R17 joins it level with the resistor
UEND = u2pin(14)[0] + 1.625         # where TX's 45-degree run ends, beside its pin
for pin, net, k, upad in (("6", "UART_RX", 3, "15"), ("7", "UART_TX", 4, "14")):
    x0, y0 = upin(pin)
    d, run = DX0 + BP * k, BUS_Y + BP * k
    px, py = u2pin(upad)
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LP = 0.5
K1L = UX - 12.6
LXS = upin(8)[0] - 1.0              # where the left pins' 45-degree exits start
t("RLY1_DRV", ("U1", "8"), (LXS, upin(8)[1]), (K1L, upin(8)[1] + LXS - K1L), (K1L, HY + 1.5), ("R23", "1"))
FAN_END = HY - 2.54 - 1.0           # the innermost lanes reach their header column here, 1 mm above the pin row
for i, (pin, hp, odd) in enumerate((("12", 8, False), ("11", 7, True), ("10", 6, False), ("9", 5, True))):
    lx = K1L + LP * (4 - i)
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HX4, HY4 = HOLES[3]
EX, SX = W - 1.0, HX4 - 2.6         # the run down the right edge, then past the screw's left side
t("RLY2_DRV", ("U1", "24"), K2V, vias=[K2V])
t("RLY2_DRV", K2V, (EX, upin(24)[1]), (EX, HY4 - 1.1 - (EX - SX)), (SX, HY4 - 1.1),
  (SX, K2V2[1] - (SX - K2V2[0])), K2V2, layer="B", vias=[K2V2], radii=[None, 2.0, 1.5, 1.5, 1.5])
t("RLY2_DRV", K2V2, ("R24", "1"))

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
